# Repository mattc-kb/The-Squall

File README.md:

# The Squall v1.1
Wireless split keyboard build based off of the Tempest which in turn is based on the Temper and Chocofi.

I wanted a splay for the outer columns, but a slightly more agressive stagger than the Tempestv2 while retaining the thumb cluster placement of the Temper and Chocofi.

Included in the repo are the ergogen config and footprint files as well as the Kicad output and gerbers for both the PCB and the plates.

### Bill of materials:
36 smd diodes  
36 Choc hotswap sockets  
2 NiceNano / nRF52840 BLE controllers  
2 JST sockets  
2 smd power switches  
2 reset switches  

## Assembly:
Soldering of the jumpers for the controller, NiceView and the power connector is done on the back of the board. The same side as the sockets and diodes.
The power switch is also intended to be mounted on the underside of board.

## Firmware:
I have loaded and I am currently using Corne firmware successfully on this board.

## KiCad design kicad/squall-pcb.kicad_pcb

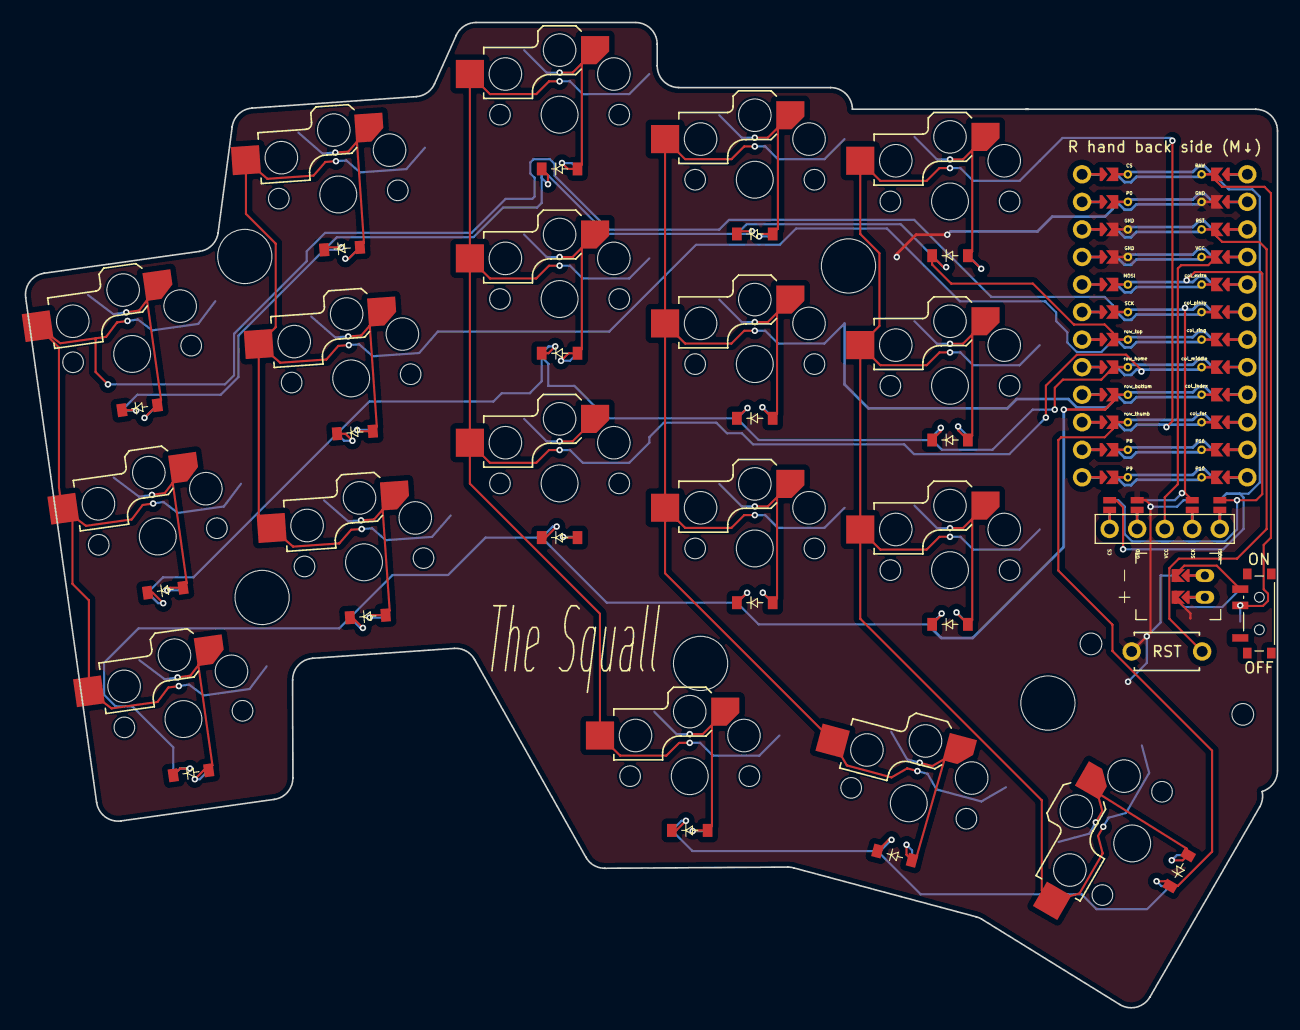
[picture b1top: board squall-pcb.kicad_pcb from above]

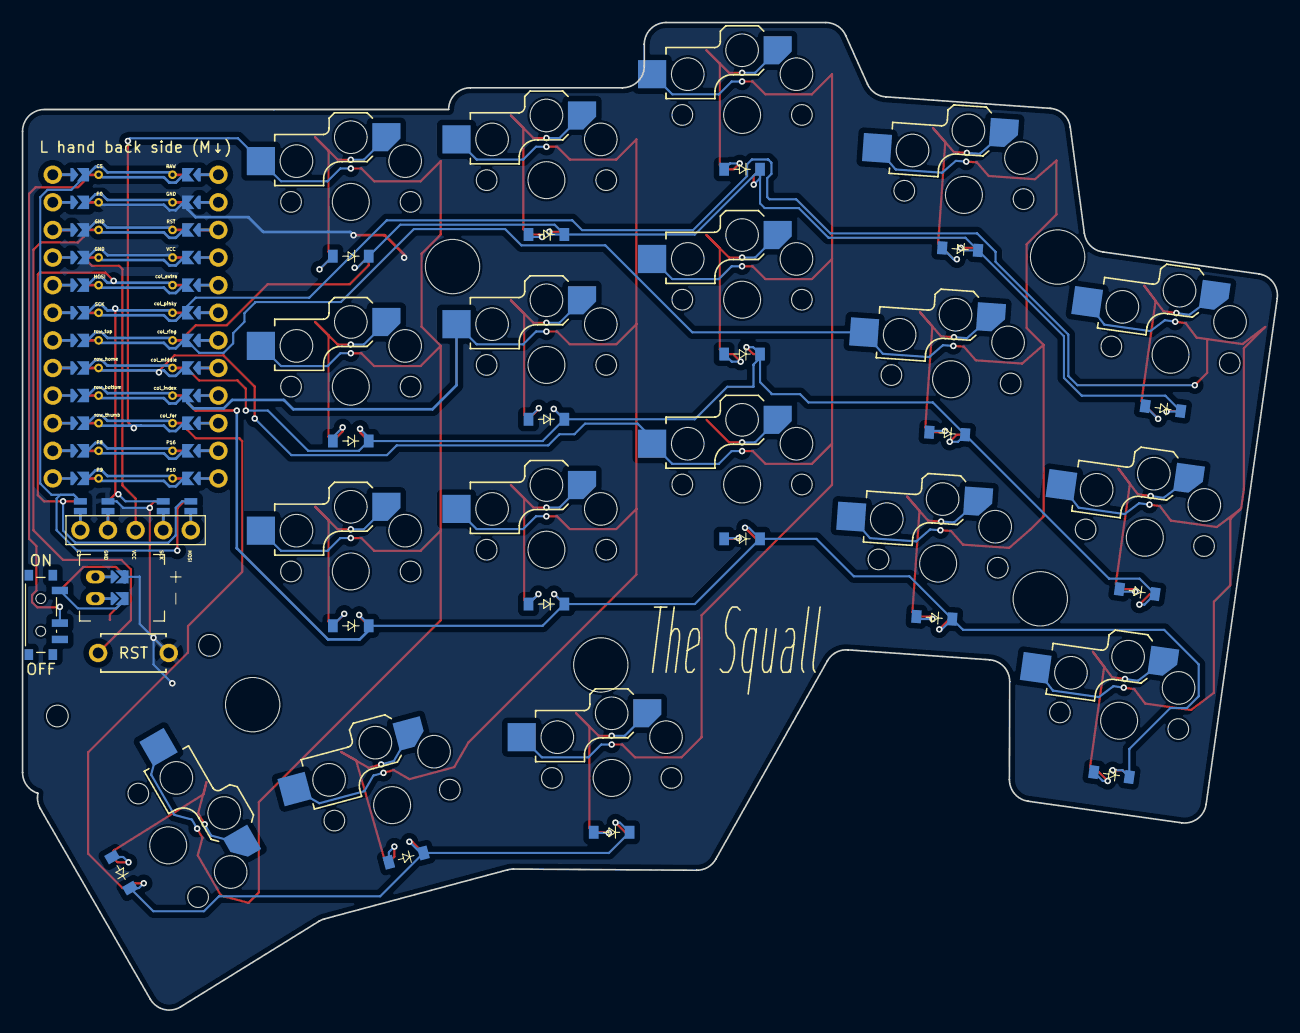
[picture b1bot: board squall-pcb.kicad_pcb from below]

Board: 2 copper layers, 115.5 x 90.9 mm, 48 parts (18 on the bottom side), 41 nets.

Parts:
D1, D2, D3, D4, D5, D6, D7, D8, D9, D10, D11, D12, D13, D14, D15, D16, D17, D18: diode_tht_sod123
DISP1: display_nice_view
JST1: battery_connector_jst_ph_2
MCU1: mcu_nice_nano
MH1, MH2, MH3, MH4, MH5, MH6, MH7: mounting_hole_npth
PWR1: power_switch_smd_side
RST1: reset_switch_tht_top
S1, S2, S3, S4, S5, S6, S7, S8, S9, S10, S11, S12, S13, S14, S15, S16, S17, S18: switch_choc_v1_v2

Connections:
BAT_P: JST1.1, PWR1.1, PWR1.3
CS: DISP1.14, DISP1.24, MCU1.124
DISP1_1: DISP1.1, DISP1.10, DISP1.23
DISP1_2: DISP1.2, DISP1.11, DISP1.22
DISP1_4: DISP1.4, DISP1.12, DISP1.21
DISP1_5: DISP1.5, DISP1.13, DISP1.20
GND: DISP1.15, DISP1.25, JST1.2, MCU1.102, MCU1.121, MCU1.122, RST1.2
JST1_1: JST1.11, JST1.21, JST1.31
JST1_2: JST1.12, JST1.22, JST1.32
MOSI: DISP1.17, DISP1.27, MCU1.120
RAW: MCU1.101, PWR1.2
RST: MCU1.103, RST1.1
SCK: DISP1.16, DISP1.26, MCU1.119
VCC: DISP1.3, MCU1.104
col_far: MCU1.110, S13.2, S14.2, S15.2, S18.2
col_index: MCU1.109, S10.2, S11.2, S12.2, S17.2
col_middle: MCU1.108, S7.2, S8.2, S9.2, S16.2
col_pinky: MCU1.106, S1.2, S2.2, S3.2
col_ring: MCU1.107, S4.2, S5.2, S6.2
far_bottom: D13.2, S13.1
far_home: D14.2, S14.1
far_top: D15.2, S15.1
index_bottom: D10.2, S10.1
index_home: D11.2, S11.1
index_top: D12.2, S12.1
inner_cluster: D16.2, S16.1
middle_bottom: D7.2, S7.1
middle_cluster: D17.2, S17.1
middle_home: D8.2, S8.1
middle_top: D9.2, S9.1
outer_cluster: D18.2, S18.1
pinky_bottom: D1.2, S1.1
pinky_home: D2.2, S2.1
pinky_top: D3.2, S3.1
ring_bottom: D4.2, S4.1
ring_home: D5.2, S5.1
ring_top: D6.2, S6.1
row_bottom: D1.1, D4.1, D7.1, D10.1, D13.1, MCU1.116
row_home: D2.1, D5.1, D8.1, D11.1, D14.1, MCU1.117
row_thumb: D16.1, D17.1, D18.1, MCU1.115
row_top: D3.1, D6.1, D9.1, D12.1, D15.1, MCU1.118

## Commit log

2025-03-24 Initial User Config.
2026-01-20 Added Ergogen and Kicad files
2026-02-07 updated README.md on minipc
2026-02-08 Added pictures folder and pictures
2026-02-08 Added pictures to README
2026-02-08 Corrected README
2026-02-09 Removed extra picture
